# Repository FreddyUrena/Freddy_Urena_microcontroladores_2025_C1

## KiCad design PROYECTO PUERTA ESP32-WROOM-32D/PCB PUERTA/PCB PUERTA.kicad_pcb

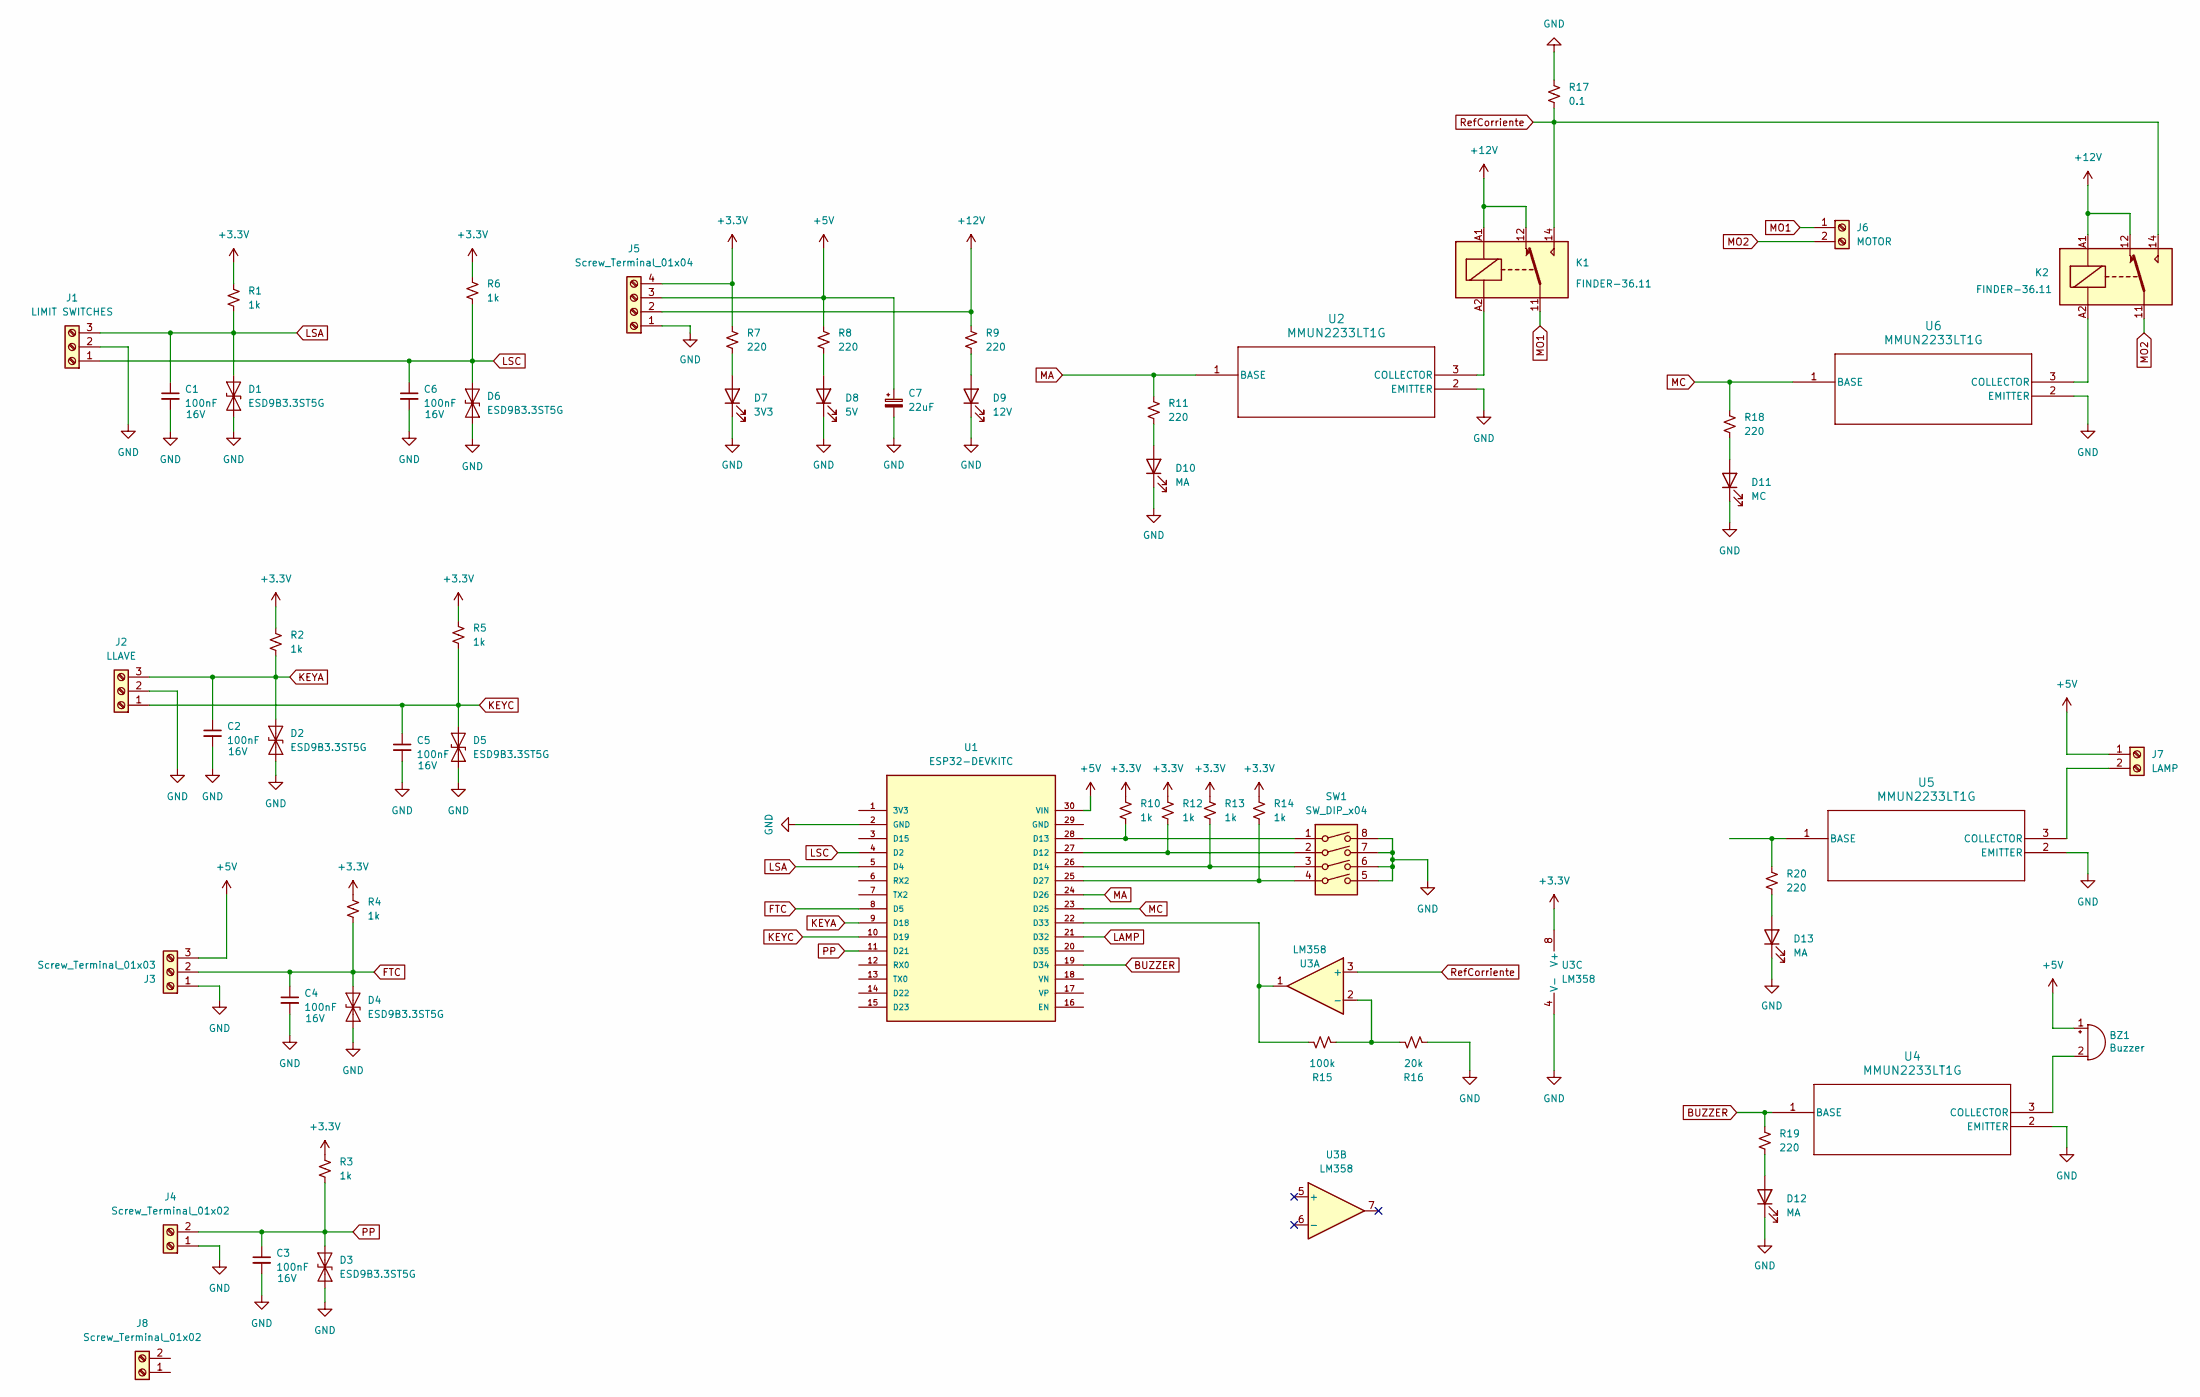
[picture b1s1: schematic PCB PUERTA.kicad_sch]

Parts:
BZ1: Buzzer; Buzzer_TDK_PS1240P02BT_D12.2mm_H6.5mm; Part number HNB09A05
C1, C2, C3, C4, C5, C6: 100nF; C_0402_1005Metric; Voltage 16V; Part number CL05B104KO5NNNC
C7: 22uF; CP_Elec_5x5.4; Part number UWT1A220MCL1GB
D1, D2, D3, D4, D5, D6: ESD9B3.3ST5G; D_SOD-923; Part number ESD9B3.3ST5G
D7: 3V3; LED_0402_1005Metric; Part number NCD0402R1
D8: 5V; LED_0402_1005Metric; Part number NCD0402R1
D9: 12V; LED_0402_1005Metric; Part number NCD0402R1
D10, D12, D13: MA; LED_0402_1005Metric; Part number NCD0402R1
D11: MC; LED_0402_1005Metric; Part number NCD0402R1
J1: LIMIT SWITCHES; TerminalBlock_bornier-3_P5.08mm; Part number YC0321500000G
J2: LLAVE; TerminalBlock_bornier-3_P5.08mm; Part number DB128V-5.08-3P-GN-S
J3: Screw_Terminal_01x03; TerminalBlock_bornier-3_P5.08mm; Part number DB128V-5.08-3P-GN-S
J4: Screw_Terminal_01x02; TerminalBlock_bornier-2_P5.08mm; Part number WJ500V-5.08-2P
J5: Screw_Terminal_01x04; TerminalBlock_bornier-4_P5.08mm; Part number DB128V-5.08-4P-GN-S
J6: MOTOR; TerminalBlock_bornier-2_P5.08mm; Part number WJ500V-5.08-2P
J7: LAMP; TerminalBlock_bornier-2_P5.08mm; Part number WJ500V-5.08-2P
J8: Screw_Terminal_01x02; CONN-TH_P5.08_KF128-5.08-2P; Part number WJ500V-5.08-2P
K1, K2: FINDER-36.11; Relay_SPDT_Finder_36.11
R1, R2, R3, R4, R5, R6, R10, R12, R13, R14: 1k; R_0402_1005Metric; Part number CRCW04021K00FKED
R7, R8, R9, R11, R18, R19, R20: 220; R_0402_1005Metric; Part number CRCW0402220RFKED
R15: 100k; C_0402_1005Metric; Part number ERJPA2J104X
R16: 20k; C_0402_1005Metric; Part number CRCW040220K0FKEDHP
R17: 0.1; R_2512_6332Metric
SW1: SW_DIP_x04; SW_DIP_SPSTx04_Slide_KingTek_DSHP04TS_W7.62mm_P1.27mm; Part number DSHP04TSGER
U1: ESP32-DEVKITC; MODULE_ESP32-DEVKITC
U2, U4, U5, U6: MMUN2233LT1G; SOT-23-3_1P4X3P040_ONS-L; Part number MMUN2233LT1G
U3: LM358; lm358; Part number LMV358IDR

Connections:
+3.3V: J5.4, R1.1, R2.1, R3.1, R4.1, R5.1, R6.1, R7.2, R10.1, R12.1, R13.1, R14.1, U3.8 (V+)
+5V: BZ1.1 (+), C7.1, J3.3, J5.3, J7.1, R8.2, U1.30 (VIN)
+12V: J5.2, K1.12, K1.A1, K2.12, K2.A1, R9.2
BUZZER: R19.2, U1.19 (D34), U4.1 (BASE)
FTC: C4.1, D4.2 (A2), J3.2, R4.2, U1.8 (D5)
GND: C1.2, C2.2, C3.2, C4.2, C5.2, C6.2, C7.2, D1.1 (A1), D2.1 (A1), D3.1 (A1), D4.1 (A1), D5.1 (A1), D6.1 (A1), D7.1 (K), D8.1 (K), D9.1 (K), D10.1 (K), D11.1 (K), D12.1 (K), D13.1 (K), J1.2, J2.2, J3.1, J4.1, J5.1, R16.2, R17.1, SW1.5, SW1.6, SW1.7, SW1.8, U1.2 (GND), U2.2 (EMITTER), U3.4 (V-), U4.2 (EMITTER), U5.2 (EMITTER), U6.2 (EMITTER)
KEYA: C2.1, D2.2 (A2), J2.3, R2.2, U1.9 (D18)
KEYC: C5.1, D5.2 (A2), J2.1, R5.2, U1.10 (D19)
LAMP: U1.21 (D32)
LSA: C1.1, D1.2 (A2), J1.3, R1.2, U1.5 (D4)
LSC: C6.1, D6.2 (A2), J1.1, R6.2, U1.4 (D2)
MA: R11.2, U1.24 (D26), U2.1 (BASE)
MC: R18.2, U1.23 (D25), U6.1 (BASE)
MO1: J6.1, K1.11
MO2: J6.2, K2.11
unnamed: BZ1.2 (-), U4.3 (COLLECTOR)
unnamed: D7.2 (A), R7.1
unnamed: D8.2 (A), R8.1
unnamed: D9.2 (A), R9.1
unnamed: D10.2 (A), R11.1
unnamed: D11.2 (A), R18.1
unnamed: D12.2 (A), R19.1
unnamed: D13.2 (A), R20.1
unnamed: J7.2, U5.3 (COLLECTOR)
unnamed: R12.2, SW1.2, U1.27 (D12)
unnamed: R10.2, SW1.1, U1.28 (D13)
unnamed: R13.2, SW1.3, U1.26 (D14)
unnamed: R14.2, SW1.4, U1.25 (D27)
unnamed: R15.1, U1.22 (D33), U3.1
unnamed: K1.A2, U2.3 (COLLECTOR)
unnamed: R15.2, R16.1, U3.2 (-)
unnamed: R20.2, U5.1 (BASE)
unnamed: K2.A2, U6.3 (COLLECTOR)
PP: C3.1, D3.2 (A2), J4.2, R3.2, U1.11 (D21)
RefCorriente: K1.14, K2.14, R17.2, U3.3 (+)

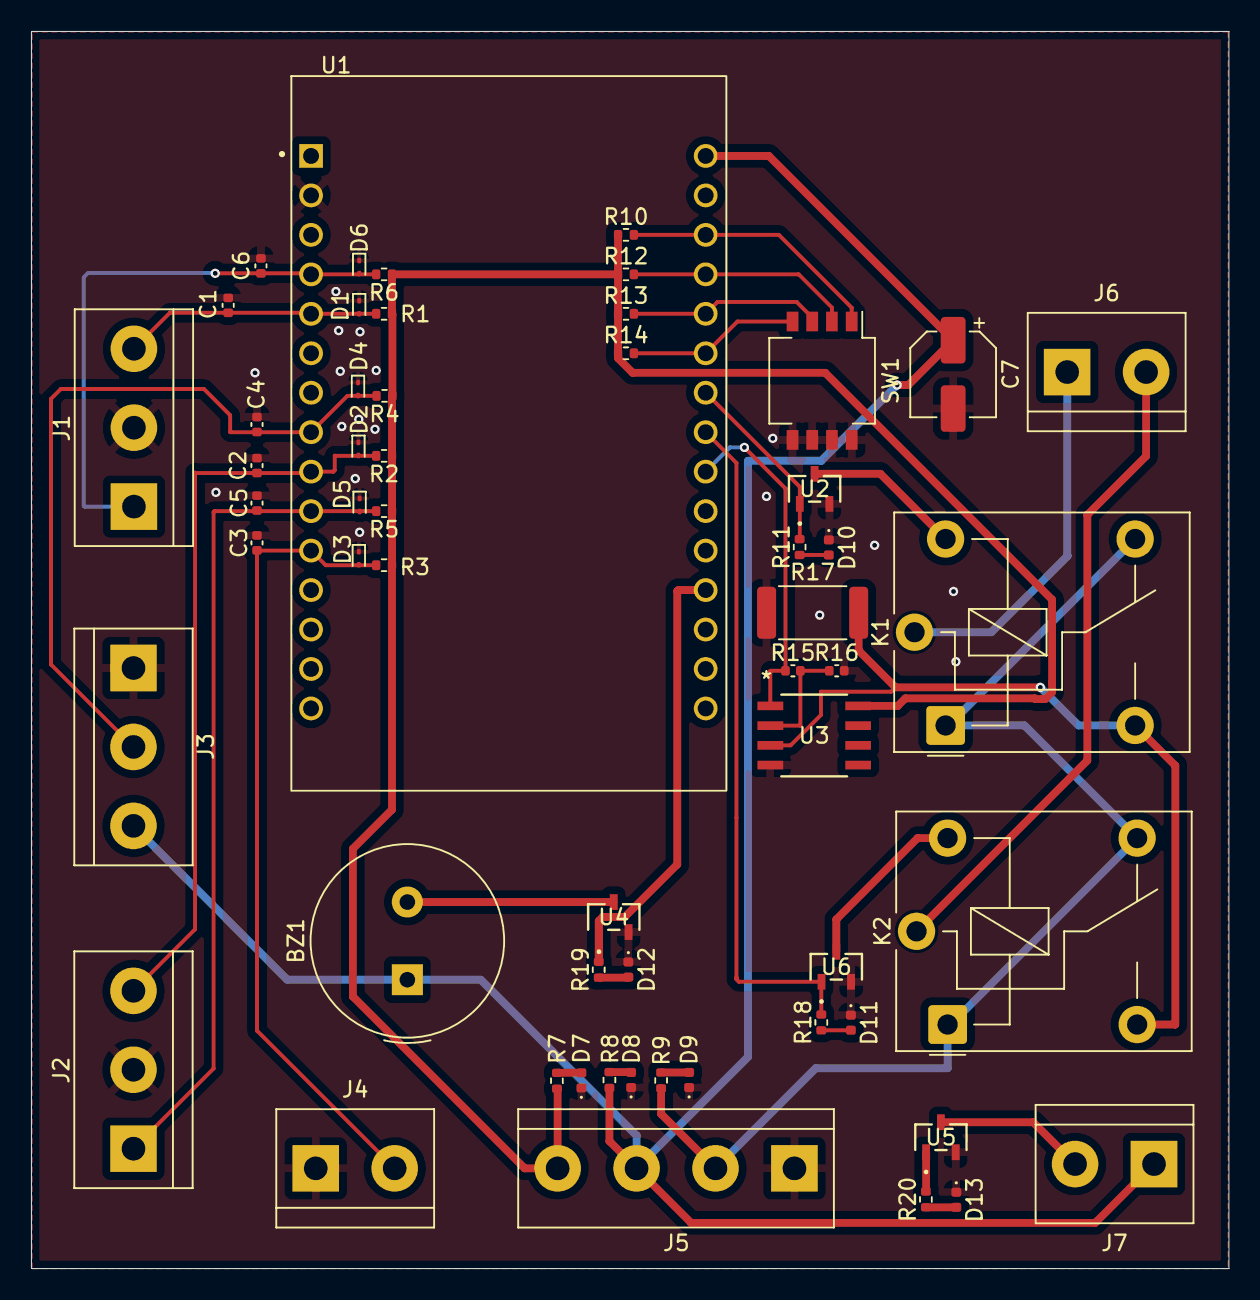
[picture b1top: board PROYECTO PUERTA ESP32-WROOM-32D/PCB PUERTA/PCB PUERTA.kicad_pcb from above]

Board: 2 copper layers, 77.1 x 79.6 mm, 57 parts (0 on the bottom side), 34 nets.

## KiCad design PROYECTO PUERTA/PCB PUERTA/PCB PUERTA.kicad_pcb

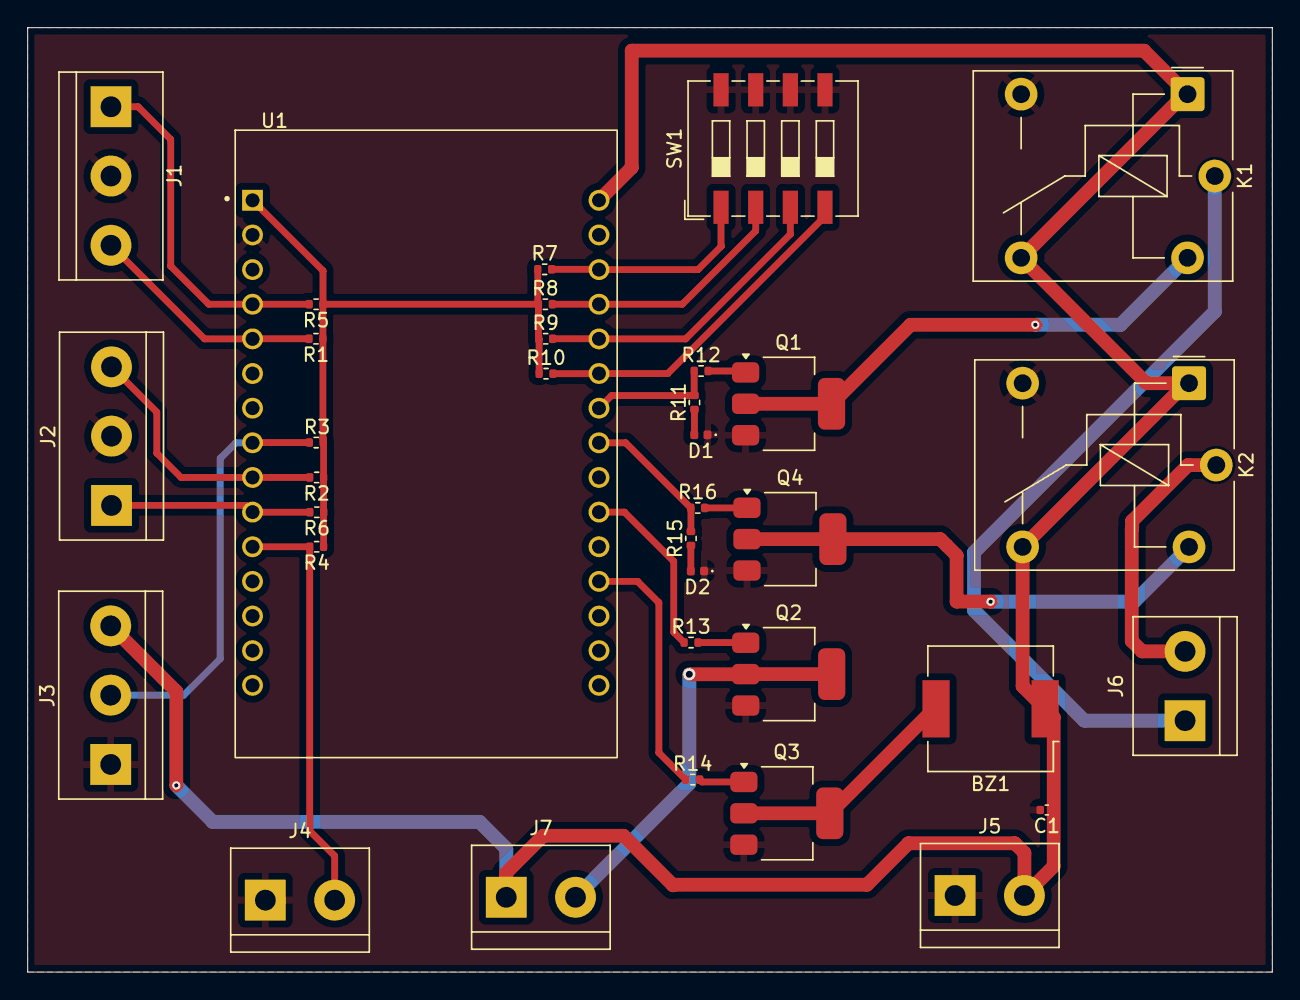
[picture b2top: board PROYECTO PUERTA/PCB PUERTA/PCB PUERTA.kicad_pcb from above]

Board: 2 copper layers, 91.3 x 69.2 mm, 35 parts (0 on the bottom side), 29 nets.

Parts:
BZ1: Buzzer; Buzzer_CUI_CPT-9019S-SMT
C1: 22u; C_0402_1005Metric
D1: MA; LED_0402_1005Metric
D2: MC; LED_0402_1005Metric
J1: LIMIT SWITCHES; TerminalBlock_bornier-3_P5.08mm
J2: LLAVE; TerminalBlock_bornier-3_P5.08mm
J3: Screw_Terminal_01x03; TerminalBlock_bornier-3_P5.08mm
J4: Screw_Terminal_01x02; TerminalBlock_bornier-2_P5.08mm
J5: ALIMENTACION; TerminalBlock_bornier-2_P5.08mm
J6: MOTOR; TerminalBlock_bornier-2_P5.08mm
J7: LAMP; TerminalBlock_bornier-2_P5.08mm
K1, K2: FINDER-36.11; Relay_SPDT_Finder_36.11
Q1, Q2, Q3, Q4: PZT2222A; SOT-223-3_TabPin2
R1, R2, R3, R4, R5, R6, R7, R8, R9, R10, R12, R13, R14, R16: 1k; R_0402_1005Metric
R11, R15: 220; R_0402_1005Metric
SW1: SW_DIP_x04; SW_DIP_SPSTx04_Slide_9.78x12.34mm_W8.61mm_P2.54mm
U1: ESP32-DEVKITC; MODULE_ESP32-DEVKITC

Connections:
+3.3V: R1.1, R2.1, R3.1, R4.1, R5.1, R6.1, R7.1, R8.1, R9.1, R10.1, U1.1 (3V3)
+5V: BZ1.1 (+), C1.1, J3.3, J5.2, J7.1, K1.12, K1.A1, K2.12, K2.A1, U1.30 (VIN)
BUZZER: R14.1, U1.19 (D34)
FTC: J3.2, R3.2, U1.8 (D5)
GND: C1.2, D1.1 (K), D2.1 (K), J1.2, J2.2, J3.1, J4.1, J5.1, K1.14, K2.14, Q1.3 (E), Q2.3 (E), Q3.3 (E), Q4.3 (E), SW1.5, SW1.6, SW1.7, SW1.8, U1.2 (GND)
KEYA: J2.3, R2.2, U1.9 (D18)
KEYC: J2.1, R6.2, U1.10 (D19)
LAMP: R13.1, U1.21 (D32)
LSA: J1.3, R1.2, U1.5 (D4)
LSC: J1.1, R5.2, U1.4 (D2)
MA: R11.2, R12.1, U1.24 (D26)
MC: R15.2, R16.1, U1.23 (D25)
MO1: J6.1, K1.11
MO2: J6.2, K2.11
unnamed: BZ1.2 (-), Q3.2 (C)
unnamed: D1.2 (A), R11.1
unnamed: D2.2 (A), R15.1
unnamed: J7.2, Q2.2 (C)
unnamed: Q1.1 (B), R12.2
unnamed: K1.A2, Q1.2 (C)
unnamed: Q2.1 (B), R13.2
unnamed: Q3.1 (B), R14.2
unnamed: Q4.1 (B), R16.2
unnamed: K2.A2, Q4.2 (C)
unnamed: R8.2, SW1.2, U1.27 (D12)
unnamed: R7.2, SW1.1, U1.28 (D13)
unnamed: R9.2, SW1.3, U1.26 (D14)
unnamed: R10.2, SW1.4, U1.25 (D27)
PP: J4.2, R4.2, U1.11 (D21)

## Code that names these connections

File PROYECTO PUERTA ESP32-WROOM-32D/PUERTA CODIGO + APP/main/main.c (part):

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#define MAX_RT 3600//Un incremento de 20 equivale a un segundo. Este tiempo en seg = MAX_TIEMPO_ABIERTA*0.050

// se definen los pines de entrada y salida
#define pin_lsc 2 // limit switch puerta cerrada
#define pin_lsa 4  // limit switch puerta abierta
#define pin_ftc 5 // fotocelda
#define pin_keya 18 
#define pin_keyc 19
#define pin_pp 21
#define pin_dpsw_DESCONOCIDO_LSB 27// dpsw de dos pines para funcionamiento a partir de desconocido y boton pp desde estado desconocido
#define pin_dpsw_DESCONOCIDO_MSB 14 
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#define pin_dpsw_DETENIDA_MSB 13
#define pin_ma 26  // motor abrir
#define pin_mc 25   // motor cerrar
#define pin_lamp 32 // lampara
#define pin_buzzer 34

int Func_SETTING_IO(void);

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
void vTimerCallback(TimerHandle_t pxTimer)
{
/*pin_lsc 2 // limit switch puerta cerrada
pin_lsa 4  // limit switch puerta abierta
pin_ftc 5 // fotocelda
pin_keya 18 
pin_keyc 19
pin_pp 21
pin_dpsw_DESCONOCIDO_LSB 27// dpsw de dos pines para funcionamiento a partir de desconocido y boton pp desde estado desconocido
pin_dpsw_DESCONOCIDO_MSB 14 
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pin_dpsw_DETENIDA_MSB 13
pin_ma 26  // motor abrir
pin_mc 25   // motor cerrar
pin_lamp 32 // lampara
pin_buzzer 34*/

    //ESP_LOGI(tag, "Event was called from timer");
    if(gpio_get_level(pin_lsc))
    {
        io.lsc = LM_ACTIVO;
    }
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        io.lsc = LM_INACTIVO;
    }

    if(gpio_get_level(pin_lsa))
    {
        io.lsa = LM_ACTIVO;
    }
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        io.lsa = LM_INACTIVO;
    }

    if(gpio_get_level(pin_ftc))
    {
        io.ftc = FTC_ACTIVO;
    }
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        io.ftc = FTC_INACTIVO;
    }

    if(gpio_get_level(pin_keya))
    {
        io.keya = KEY_ACTIVO;
    }
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        io.keya = KEY_INACTIVO;
    }

    if(gpio_get_level(pin_keyc))
    {
        io.keyc = KEY_ACTIVO;
    }
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
    if(io.lamp == LAMP_ON)
    {
        gpio_set_level(pin_lamp, LAMP_ON);
    }

    else 
    {
        gpio_set_level(pin_lamp, LAMP_OFF);
    }

    if(io.buzzer == BUZZER_ON)
    {
        gpio_set_level(pin_buzzer, BUZZER_ON);
    }

    else
    {
        gpio_set_level(pin_buzzer, BUZZER_OFF); 
    }

    //contador para cerrar puerta automaticamente si permance abierta un tiempo excesivo
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
int Func_SETTING_IO(void)
{
/*pin_lsc 2 // limit switch puerta cerrada
pin_lsa 4  // limit switch puerta abierta
pin_ftc 5 // fotocelda
pin_keya 18 
pin_keyc 19
pin_pp 21
pin_dpsw_DESCONOCIDO[0] 27// dpsw de dos pines para funcionamiento a partir de desconocido y boton pp desde estado desconocido
pin_dpsw_DESCONOCIDO[1] 14 
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pin_dpsw_DETENIDA[1]13
pin_ma 26  // motor abrir
pin_mc 25   // motor cerrar
pin_lamp 32 // lampara
pin_buzzer 34*/

gpio_reset_pin(pin_lsc);
gpio_reset_pin(pin_lsa);
gpio_reset_pin(pin_ftc);
gpio_reset_pin(pin_keya);
gpio_reset_pin(pin_keyc);
gpio_reset_pin(pin_pp);
gpio_reset_pin(pin_dpsw_DESCONOCIDO_LSB);
gpio_reset_pin(pin_dpsw_DESCONOCIDO_MSB);
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
gpio_reset_pin(pin_ma);
gpio_reset_pin(pin_mc);
gpio_reset_pin(pin_lamp);
gpio_reset_pin(pin_buzzer);

gpio_set_direction(pin_lsa, GPIO_MODE_INPUT);
gpio_set_direction(pin_lsc, GPIO_MODE_INPUT);
gpio_set_direction(pin_ftc, GPIO_MODE_INPUT);
gpio_set_direction(pin_keya, GPIO_MODE_INPUT);
gpio_set_direction(pin_keyc, GPIO_MODE_INPUT);
gpio_set_direction(pin_pp, GPIO_MODE_INPUT);
gpio_set_direction(pin_dpsw_DESCONOCIDO_LSB, GPIO_MODE_INPUT);
gpio_set_direction(pin_dpsw_DESCONOCIDO_MSB, GPIO_MODE_INPUT);
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
gpio_set_direction(pin_ma, GPIO_MODE_OUTPUT);
gpio_set_direction(pin_mc, GPIO_MODE_OUTPUT);
gpio_set_direction(pin_lamp, GPIO_MODE_OUTPUT);
gpio_set_direction(pin_buzzer, GPIO_MODE_OUTPUT);

ESP_LOGI(tag, "Entradas asignadas");
return 0;
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
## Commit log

2025-02-12 primera tarea
2025-02-13 MAQUINA DE ESTADOS PUERTA
2025-02-13 codigo puerta completa
2025-02-13 freddy commit
2025-02-14 13.02.25.8.10
2025-02-14 Moví archivos a una nueva carpeta
2025-02-14 Actualizando estructura del repositorio
2025-02-14 13.02.25.11.43
2025-02-14 13.02.25.11.46
2025-02-14 13.02.25.11.52
2025-03-20 20.03.2025
2025-04-10 agregando emulador NE555
2025-04-15 almost there
2025-04-26 25.04.25
2025-04-26 done
